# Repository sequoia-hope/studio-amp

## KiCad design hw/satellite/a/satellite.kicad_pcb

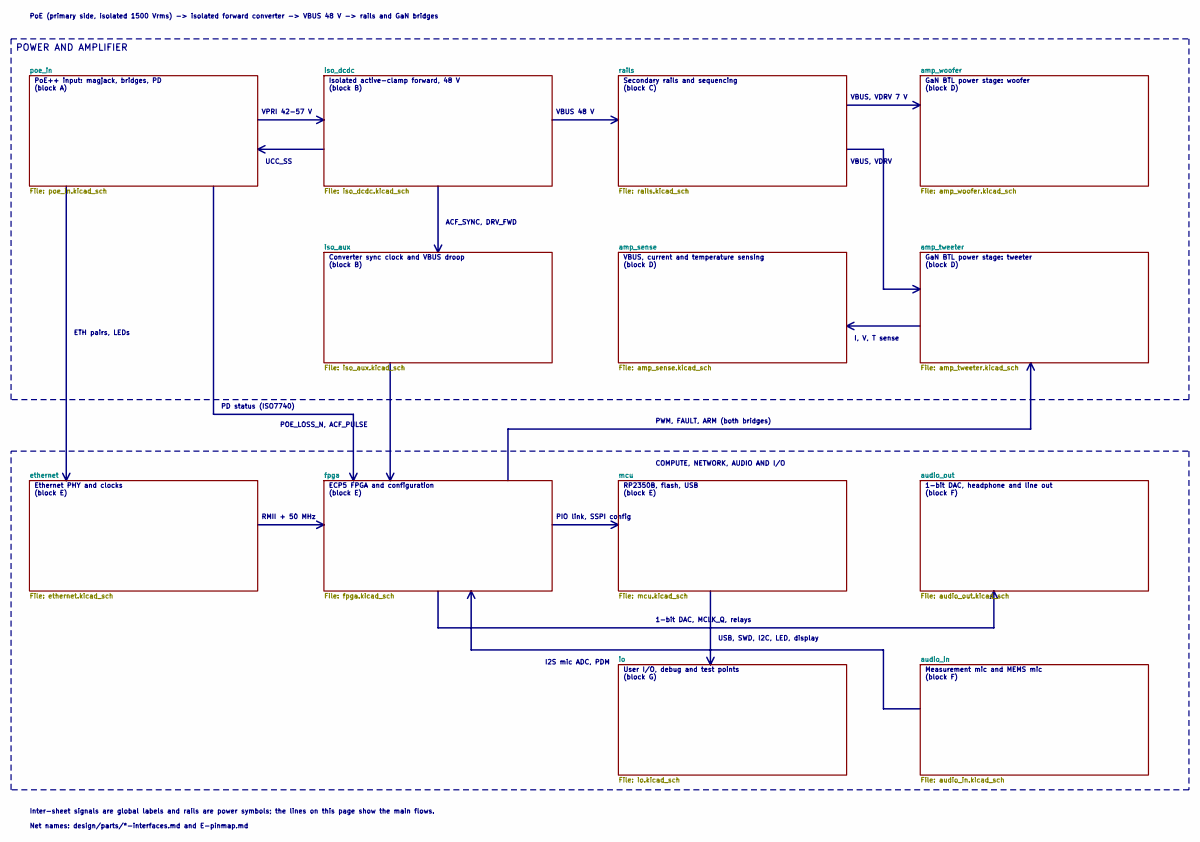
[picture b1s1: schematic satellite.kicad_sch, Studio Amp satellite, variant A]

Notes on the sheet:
PoE++ input: magjack, bridges, PD (block A)
Isolated active-clamp forward, 48 V (block B)
Converter sync clock and VBUS droop (block B)
Secondary rails and sequencing (block C)
GaN BTL power stage: woofer (block D)
GaN BTL power stage: tweeter (block D)
VBUS, current and temperature sensing (block D)
RP2350B, flash, USB (block E)
ECP5 FPGA and configuration (block E)
Ethernet PHY and clocks (block E)
1-bit DAC, headphone and line out (block F)
Measurement mic and MEMS mic (block F)
User I/O, debug and test points (block G)
VPRI 42-57 V
UCC_SS
VBUS 48 V
VBUS, VDRV 7 V
VBUS, VDRV
ACF_SYNC, DRV_FWD
I, V, T sense
ETH pairs, LEDs
RMII + 50 MHz
PIO link, SSPI config
PWM, FAULT, ARM (both bridges)
POE_LOSS_N, ACF_PULSE
1-bit DAC, MCLK_Q, relays
I2S mic ADC, PDM
USB, SWD, I2C, LED, display
PD status (ISO7740)
POWER AND AMPLIFIER
PoE (primary side, isolated 1500 Vrms) -> isolated forward converter -> VBUS 48 V -> rails and GaN bridges
Inter-sheet signals are global labels and rails are power symbols; the lines on this page show the main flows.
Net names: design/parts/*-interfaces.md and E-pinmap.md
COMPUTE, NETWORK, AUDIO AND I/O

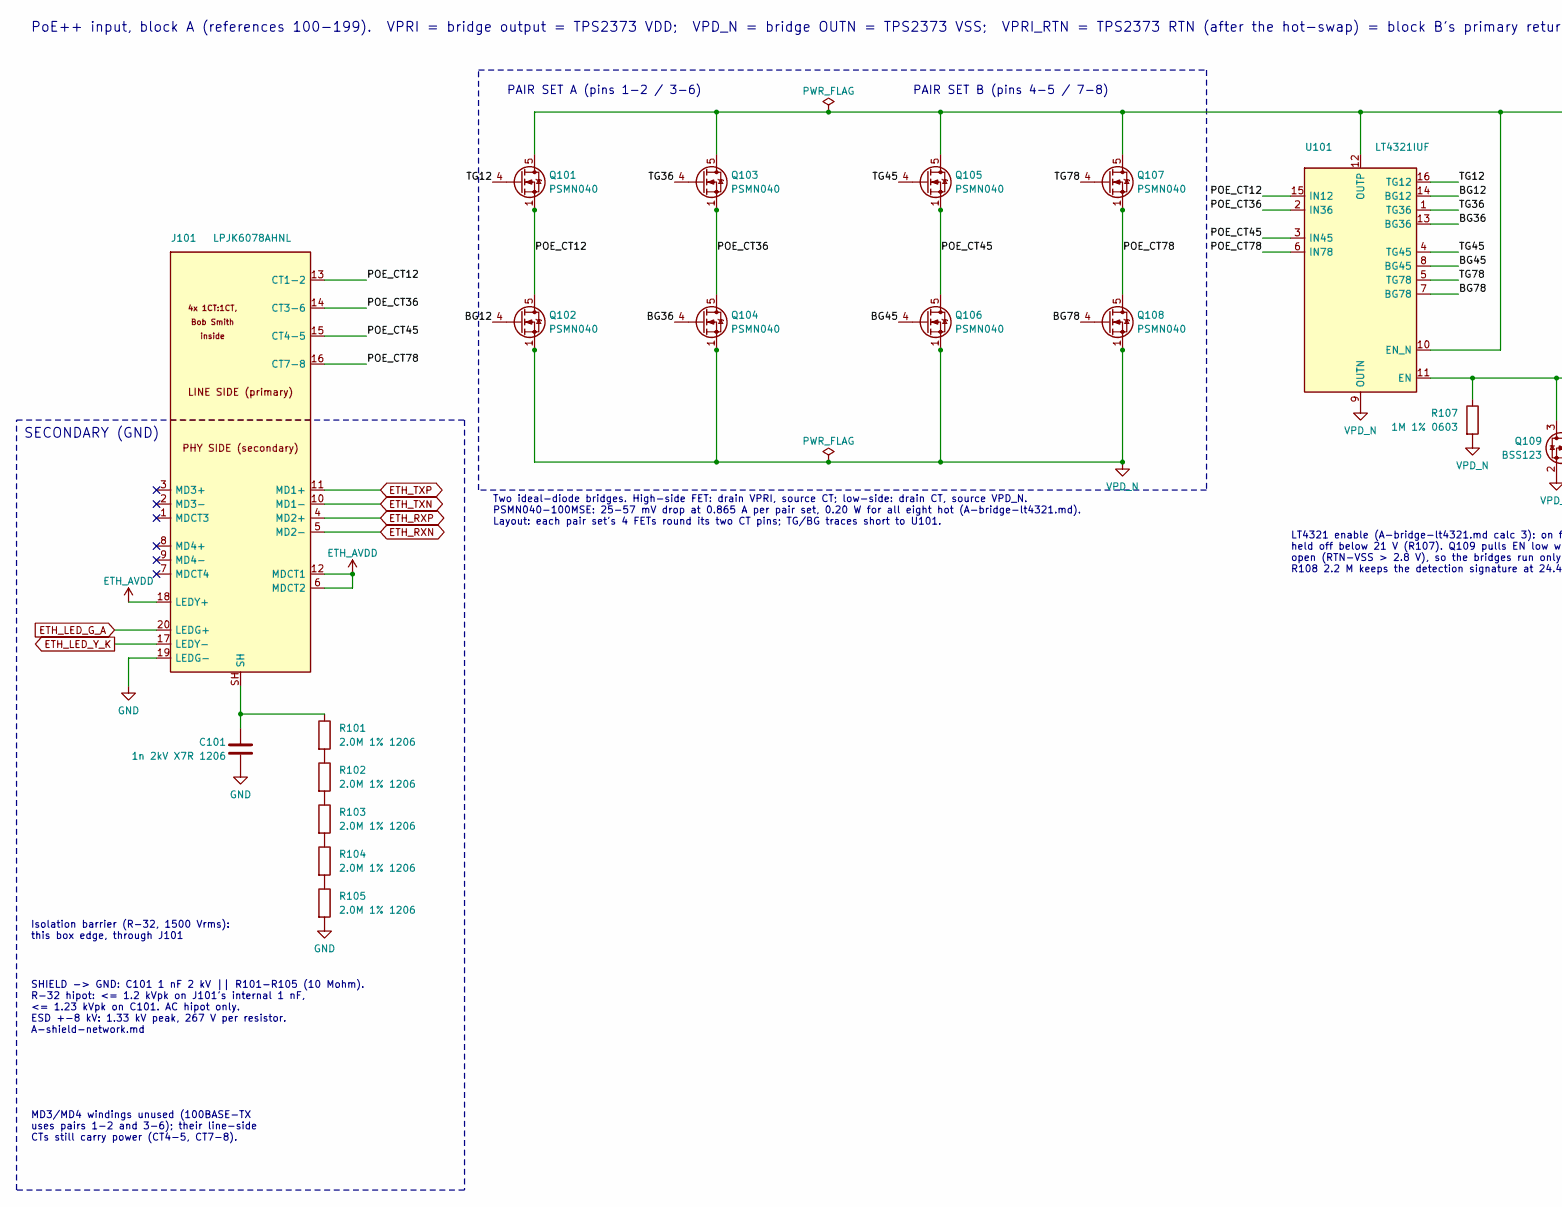
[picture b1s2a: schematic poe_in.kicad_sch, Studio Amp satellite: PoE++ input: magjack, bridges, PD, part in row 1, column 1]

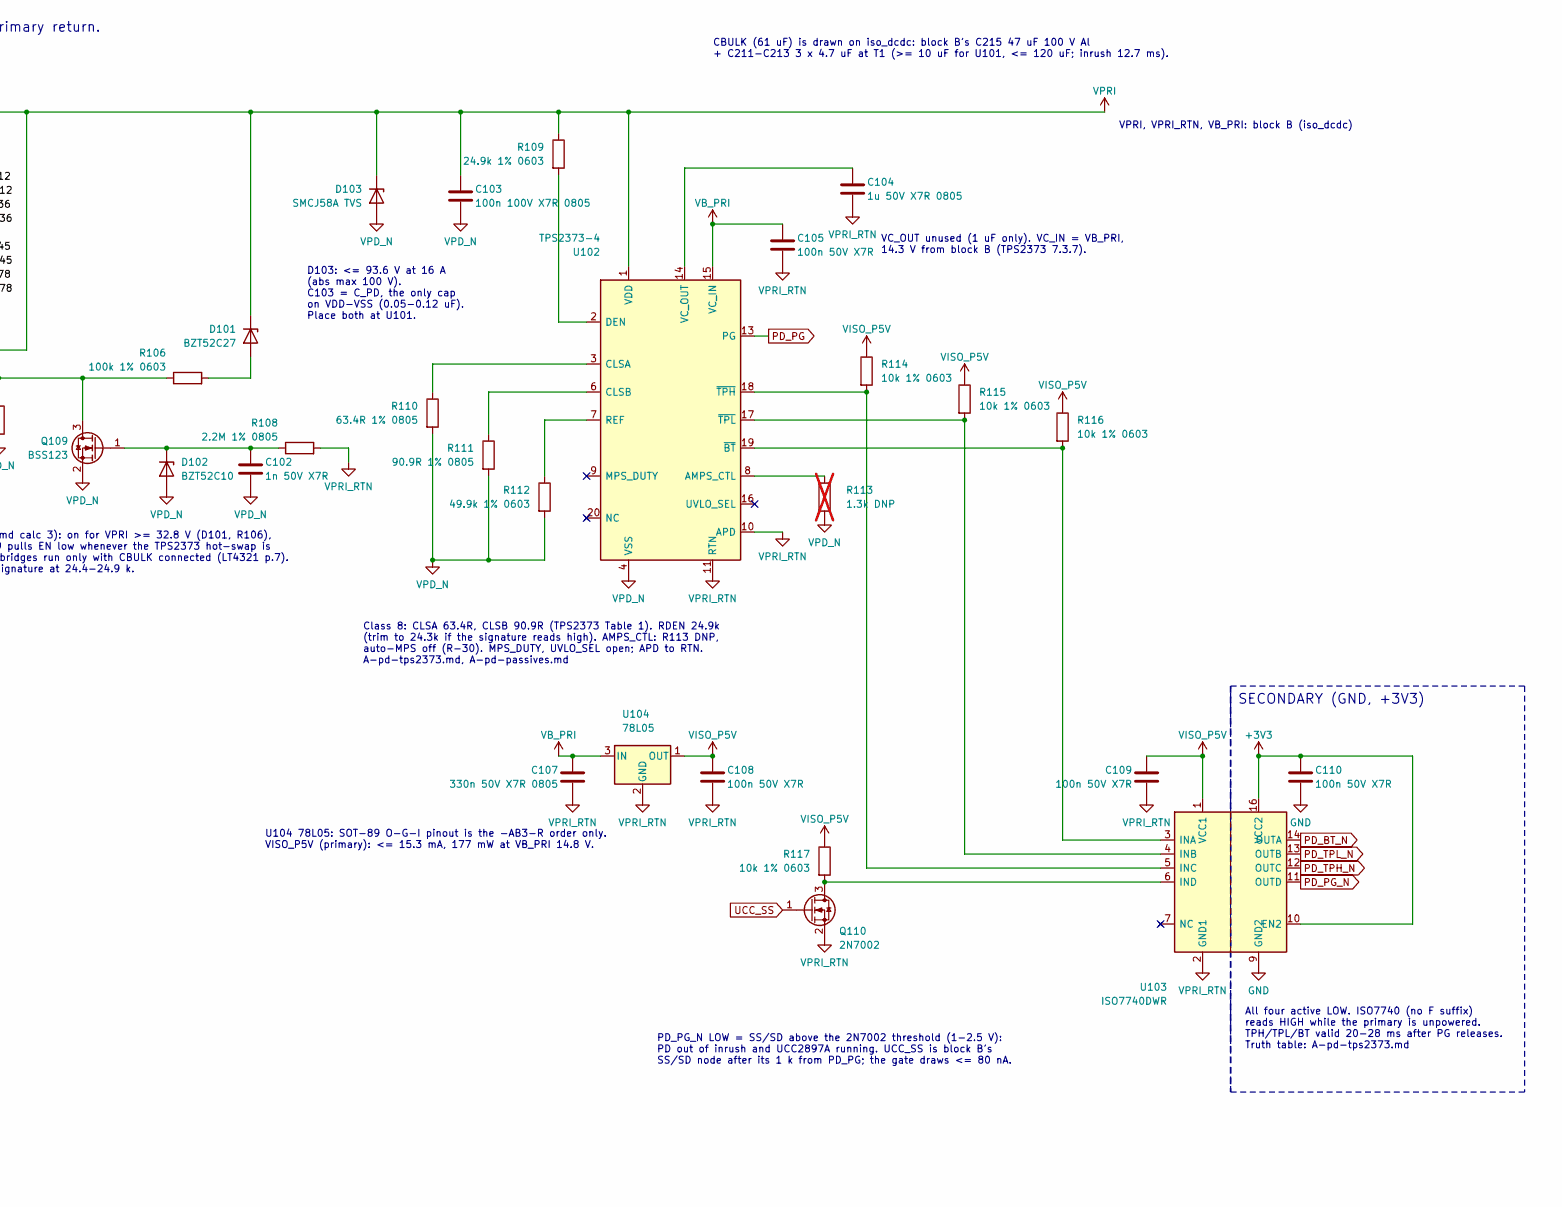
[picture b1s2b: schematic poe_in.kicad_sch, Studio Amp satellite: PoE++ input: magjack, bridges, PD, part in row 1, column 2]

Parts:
C101: 1n 2kV X7R 1206; C_1206_3216Metric; MPN 1206B102K202NT; LCSC C9196
C102: 1n 50V X7R; C_0603_1608Metric; MPN CL10B102KB8NNNC; LCSC C1588
C103: 100n 100V X7R 0805; C_0805_2012Metric; MPN CL21B104KCFNNNE; LCSC C28233
C104: 1u 50V X7R 0805; C_0805_2012Metric; MPN CL21B105KBFNNNE; LCSC C28323
C105, C108, C109, C110: 100n 50V X7R; C_0603_1608Metric; MPN CC0603KRX7R9BB104; LCSC C14663
C107: 330n 50V X7R 0805; C_0805_2012Metric; MPN 0805B334K500NT; LCSC C1740
D101: BZT52C27; D_SOD-123; MPN BZT52C27; LCSC C173421
D102: BZT52C10; D_SOD-123; MPN BZT52C10; LCSC C173431
D103: SMCJ58A TVS; D_SMC; MPN SMCJ58A-13-F; LCSC C135180
J101: LPJK6078AHNL; LINKPP_LPJK6078AHNL_RJ45_PoE; MPN LPJK6078AHNL; LCSC C49274795
Q101, Q102, Q103, Q104, Q105, Q106, Q107, Q108: PSMN040; LFPAK33; MPN PSMN040-100MSEX; LCSC C458214
Q109: BSS123; SOT-23; MPN BSS123,215; LCSC C78962
Q110: 2N7002; SOT-23; MPN 2N7002; LCSC C8545
R101, R102, R103, R104, R105: 2.0M 1% 1206; R_1206_3216Metric; MPN FRC1206F2004TS; LCSC C2907380
R106: 100k 1% 0603; R_0603_1608Metric; MPN 0603WAF1003T5E; LCSC C25803
R107: 1M 1% 0603; R_0603_1608Metric; MPN 0603WAF1004T5E; LCSC C22935
R108: 2.2M 1% 0805; R_0805_2012Metric; MPN 0805W8F2204T5E; LCSC C26113
R109: 24.9k 1% 0603; R_0603_1608Metric; MPN 0603WAF2492T5E; LCSC C25962
R110: 63.4R 1% 0805; R_0805_2012Metric; MPN FRC0805F63R4TS; LCSC C5159721
R111: 90.9R 1% 0805; R_0805_2012Metric; MPN FRC0805F90R9TS; LCSC C3000584
R112: 49.9k 1% 0603; R_0603_1608Metric; MPN 0603WAF4992T5E; LCSC C23184
R113: 1.3k DNP; R_1206_3216Metric; MPN FRC1206F1301TS; LCSC C2933592; not fitted
R114, R115, R116, R117: 10k 1% 0603; R_0603_1608Metric; MPN 0603WAF1002T5E; LCSC C25804
U101: LT4321IUF; QFN-16-1EP_4x4mm_P0.65mm_EP2.15x2.15mm; MPN LT4321IUF#TRPBF; LCSC C580183
U102: TPS2373-4; TI_RGW0020B_VQFN-20-1EP_5x5mm_P0.65mm_EP2.2x2.2mm; MPN TPS2373-4RGWR; LCSC C470963
U103: ISO7740DWR; SOIC-16W_7.5x10.3mm_P1.27mm; MPN ISO7740DWR; LCSC C529547
U104: 78L05; SOT-89-3; MPN 78L05G-AB3-R; LCSC C71136

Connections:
/poe_in/BG12: Q102.4 (G), U101.14 (BG12)
/poe_in/BG36: Q104.4 (G), U101.13 (BG36)
/poe_in/BG45: Q106.4 (G), U101.8 (BG45)
/poe_in/BG78: Q108.4 (G), U101.7 (BG78)
/poe_in/POE_CT12: J101.13 (CT1-2), Q101.1 (S), Q101.2 (S), Q101.3 (S), Q102.5 (D), U101.15 (IN12)
/poe_in/POE_CT36: J101.14 (CT3-6), Q103.1 (S), Q103.2 (S), Q103.3 (S), Q104.5 (D), U101.2 (IN36)
/poe_in/POE_CT45: J101.15 (CT4-5), Q105.1 (S), Q105.2 (S), Q105.3 (S), Q106.5 (D), U101.3 (IN45)
/poe_in/POE_CT78: J101.16 (CT7-8), Q107.1 (S), Q107.2 (S), Q107.3 (S), Q108.5 (D), U101.6 (IN78)
/poe_in/TG12: Q101.4 (G), U101.16 (TG12)
/poe_in/TG36: Q103.4 (G), U101.1 (TG36)
/poe_in/TG45: Q105.4 (G), U101.4 (TG45)
/poe_in/TG78: Q107.4 (G), U101.5 (TG78)
ETH_LED_G_A: J101.20 (LEDG+); also elsewhere on the board
ETH_LED_Y_K: J101.17 (LEDY-); also elsewhere on the board
ETH_RXN: J101.5 (MD2-); also elsewhere on the board
ETH_RXP: J101.4 (MD2+); also elsewhere on the board
ETH_TXN: J101.10 (MD1-); also elsewhere on the board
ETH_TXP: J101.11 (MD1+); also elsewhere on the board
unnamed: C101.1, J101.SH, R101.1
unnamed: D101.2 (A), R106.2
unnamed: C102.1, D102.1 (K), Q109.1 (G), R108.1
unnamed: Q109.3 (D), R106.1, R107.1, U101.11 (EN)
unnamed: Q110.3 (D), R117.2, U103.6 (IND)
unnamed: R101.2, R102.1
unnamed: R102.2, R103.1
unnamed: R103.2, R104.1
unnamed: R104.2, R105.1
unnamed: R113.1, U102.8 (AMPS_CTL)
unnamed: R110.1, U102.3 (CLSA)
unnamed: R111.1, U102.6 (CLSB)
unnamed: R109.2, U102.2 (DEN)
unnamed: R112.1, U102.7 (REF)
unnamed: C104.1, U102.14 (VC_OUT)
unnamed: R116.2, U102.19 (~BT), U103.3 (INA)
unnamed: R114.2, U102.18 (~TPH), U103.5 (INC)
unnamed: R115.2, U102.17 (~TPL), U103.4 (INB)
PD_BT_N: U103.14 (OUTA); also elsewhere on the board
PD_PG: U102.13 (PG); also elsewhere on the board
PD_PG_N: U103.11 (OUTD); also elsewhere on the board
PD_TPH_N: U103.12 (OUTC); also elsewhere on the board
PD_TPL_N: U103.13 (OUTB); also elsewhere on the board
UCC_SS: Q110.1 (G); also elsewhere on the board
VISO_P5V: C108.1, C109.1, R114.1, R115.1, R116.1, R117.1, U103.1 (VCC1), U104.1 (OUT)
VPD_N: C102.2, C103.2, D102.2 (A), D103.2 (A), Q102.1 (S), Q102.2 (S), Q102.3 (S), Q104.1 (S), Q104.2 (S), Q104.3 (S), Q106.1 (S), Q106.2 (S), Q106.3 (S), Q108.1 (S), Q108.2 (S), Q108.3 (S), Q109.2 (S), R107.2, R110.2, R111.2, R112.2, R113.2, U101.9 (OUTN), U101.17 (OUTN), U102.4 (VSS), U102.5 (VSS), U102.21 (VSS)
VPRI: C103.1, D101.1 (K), D103.1 (K), Q101.5 (D), Q103.5 (D), Q105.5 (D), Q107.5 (D), R109.1, U101.10 (EN_N), U101.12 (OUTP), U102.1 (VDD); also elsewhere on the board
VPRI_RTN: C104.2, C105.2, C107.2, C108.2, C109.2, Q110.2 (S), R108.2, U102.10 (APD), U102.11 (RTN), U102.12 (RTN), U103.2 (GND1), U103.8 (GND1), U104.2 (GND); also elsewhere on the board

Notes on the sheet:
PoE++ input, block A (references 100-199). VPRI = bridge output = TPS2373 VDD; VPD_N = bridge OUTN = TPS2373 VSS; VPRI_RTN = TPS2373 RTN (after the hot-swap) = block B's primary return.
SHIELD -> GND: C101 1 nF 2 kV || R101-R105 (10 Mohm). R-32 hipot: <= 1.2 kVpk on J101's internal 1 nF, <= 1.23 kVpk on C101. AC hipot only. ESD +-8 kV: 1.33 kV peak, 267 V per resistor. A-shield-network.md
MD3/MD4 windings unused (100BASE-TX uses pairs 1-2 and 3-6); their line-side CTs still carry power (CT4-5, CT7-8).
SECONDARY (GND)
Isolation barrier (R-32, 1500 Vrms): this box edge, through J101
PAIR SET A (pins 1-2 / 3-6)
PAIR SET B (pins 4-5 / 7-8)
Two ideal-diode bridges. High-side FET: drain VPRI, source CT; low-side: drain CT, source VPD_N. PSMN040-100MSE: 25-57 mV drop at 0.865 A per pair set, 0.20 W for all eight hot (A-bridge-lt4321.md). Layout: each pair set's 4 FETs round its two CT pins; TG/BG traces short to U101.
LT4321 enable (A-bridge-lt4321.md calc 3): on for VPRI >= 32.8 V (D101, R106), held off below 21 V (R107). Q109 pulls EN low whenever the TPS2373 hot-swap is open (RTN-VSS > 2.8 V), so the bridges run only with CBULK connected (LT4321 p.7). R108 2.2 M keeps the detection signature at 24.4-24.9 k.
D103: <= 93.6 V at 16 A (abs max 100 V). C103 = C_PD, the only cap on VDD-VSS (0.05-0.12 uF). Place both at U101.
Class 8: CLSA 63.4R, CLSB 90.9R (TPS2373 Table 1). RDEN 24.9k (trim to 24.3k if the signature reads high). AMPS_CTL: R113 DNP, auto-MPS off (R-30). MPS_DUTY, UVLO_SEL open; APD to RTN. A-pd-tps2373.md, A-pd-passives.md
VC_OUT unused (1 uF only). VC_IN = VB_PRI, 14.3 V from block B (TPS2373 7.3.7).
CBULK (61 uF) is drawn on iso_dcdc: block B's C215 47 uF 100 V Al + C211-C213 3 x 4.7 uF at T1 (>= 10 uF for U101, <= 120 uF; inrush 12.7 ms).
VPRI, VPRI_RTN, VB_PRI: block B (iso_dcdc)
PD_PG_N LOW = SS/SD above the 2N7002 threshold (1-2.5 V): PD out of inrush and UCC2897A running. UCC_SS is block B's SS/SD node after its 1 k from PD_PG; the gate draws <= 80 nA.
U104 78L05: SOT-89 O-G-I pinout is the -AB3-R order only. VISO_P5V (primary): <= 15.3 mA, 177 mW at VB_PRI 14.8 V.
SECONDARY (GND, +3V3)
All four active LOW. ISO7740 (no F suffix) reads HIGH while the primary is unpowered. TPH/TPL/BT valid 20-28 ms after PG releases. Truth table: A-pd-tps2373.md

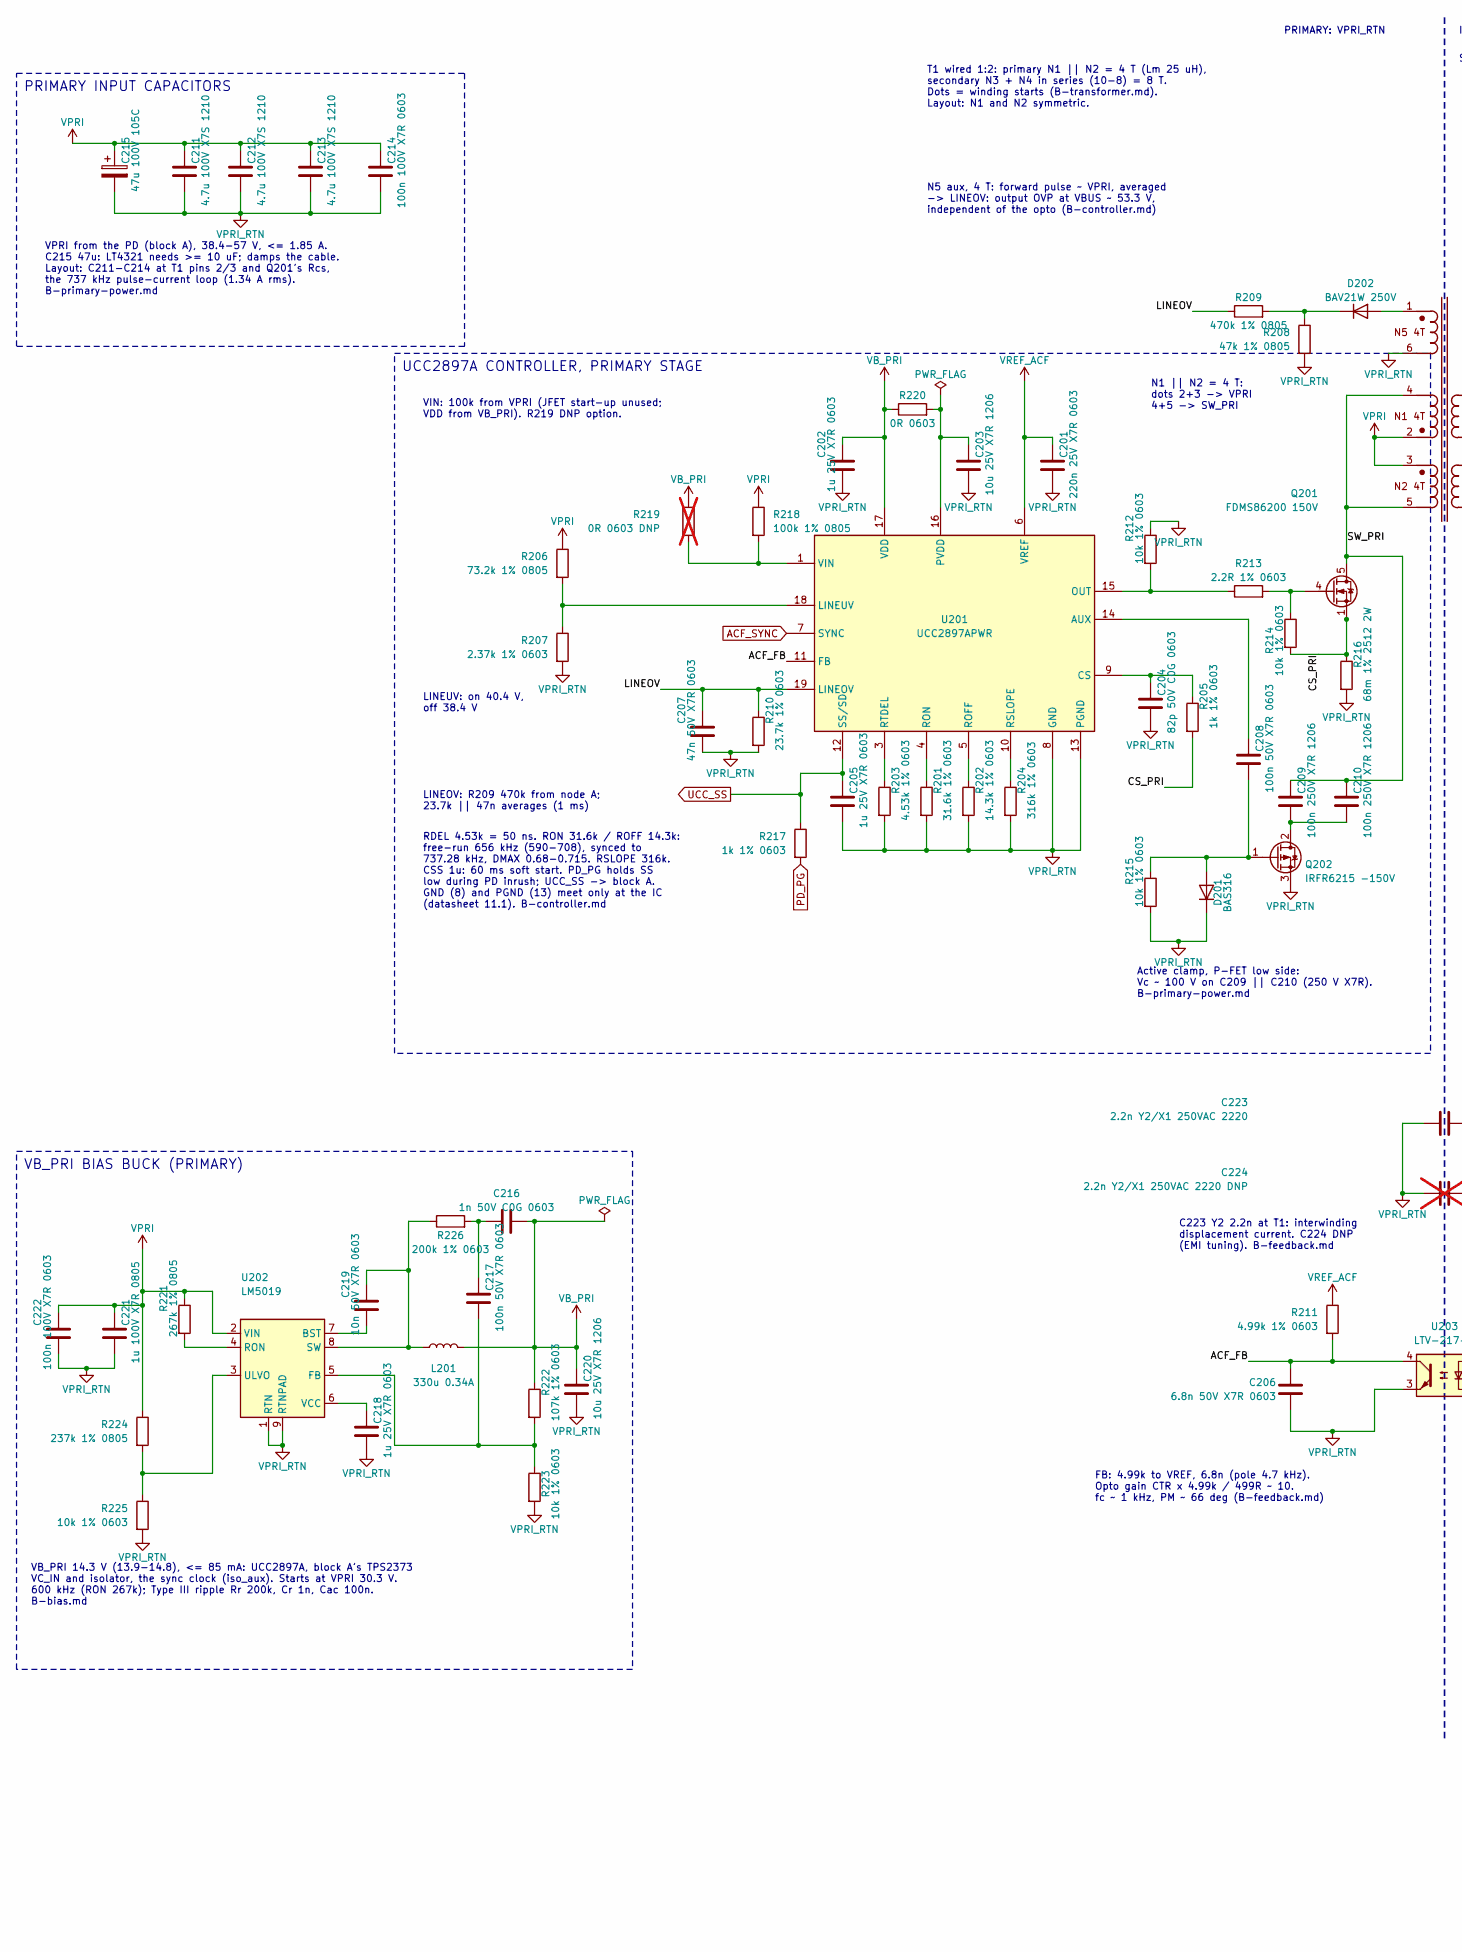
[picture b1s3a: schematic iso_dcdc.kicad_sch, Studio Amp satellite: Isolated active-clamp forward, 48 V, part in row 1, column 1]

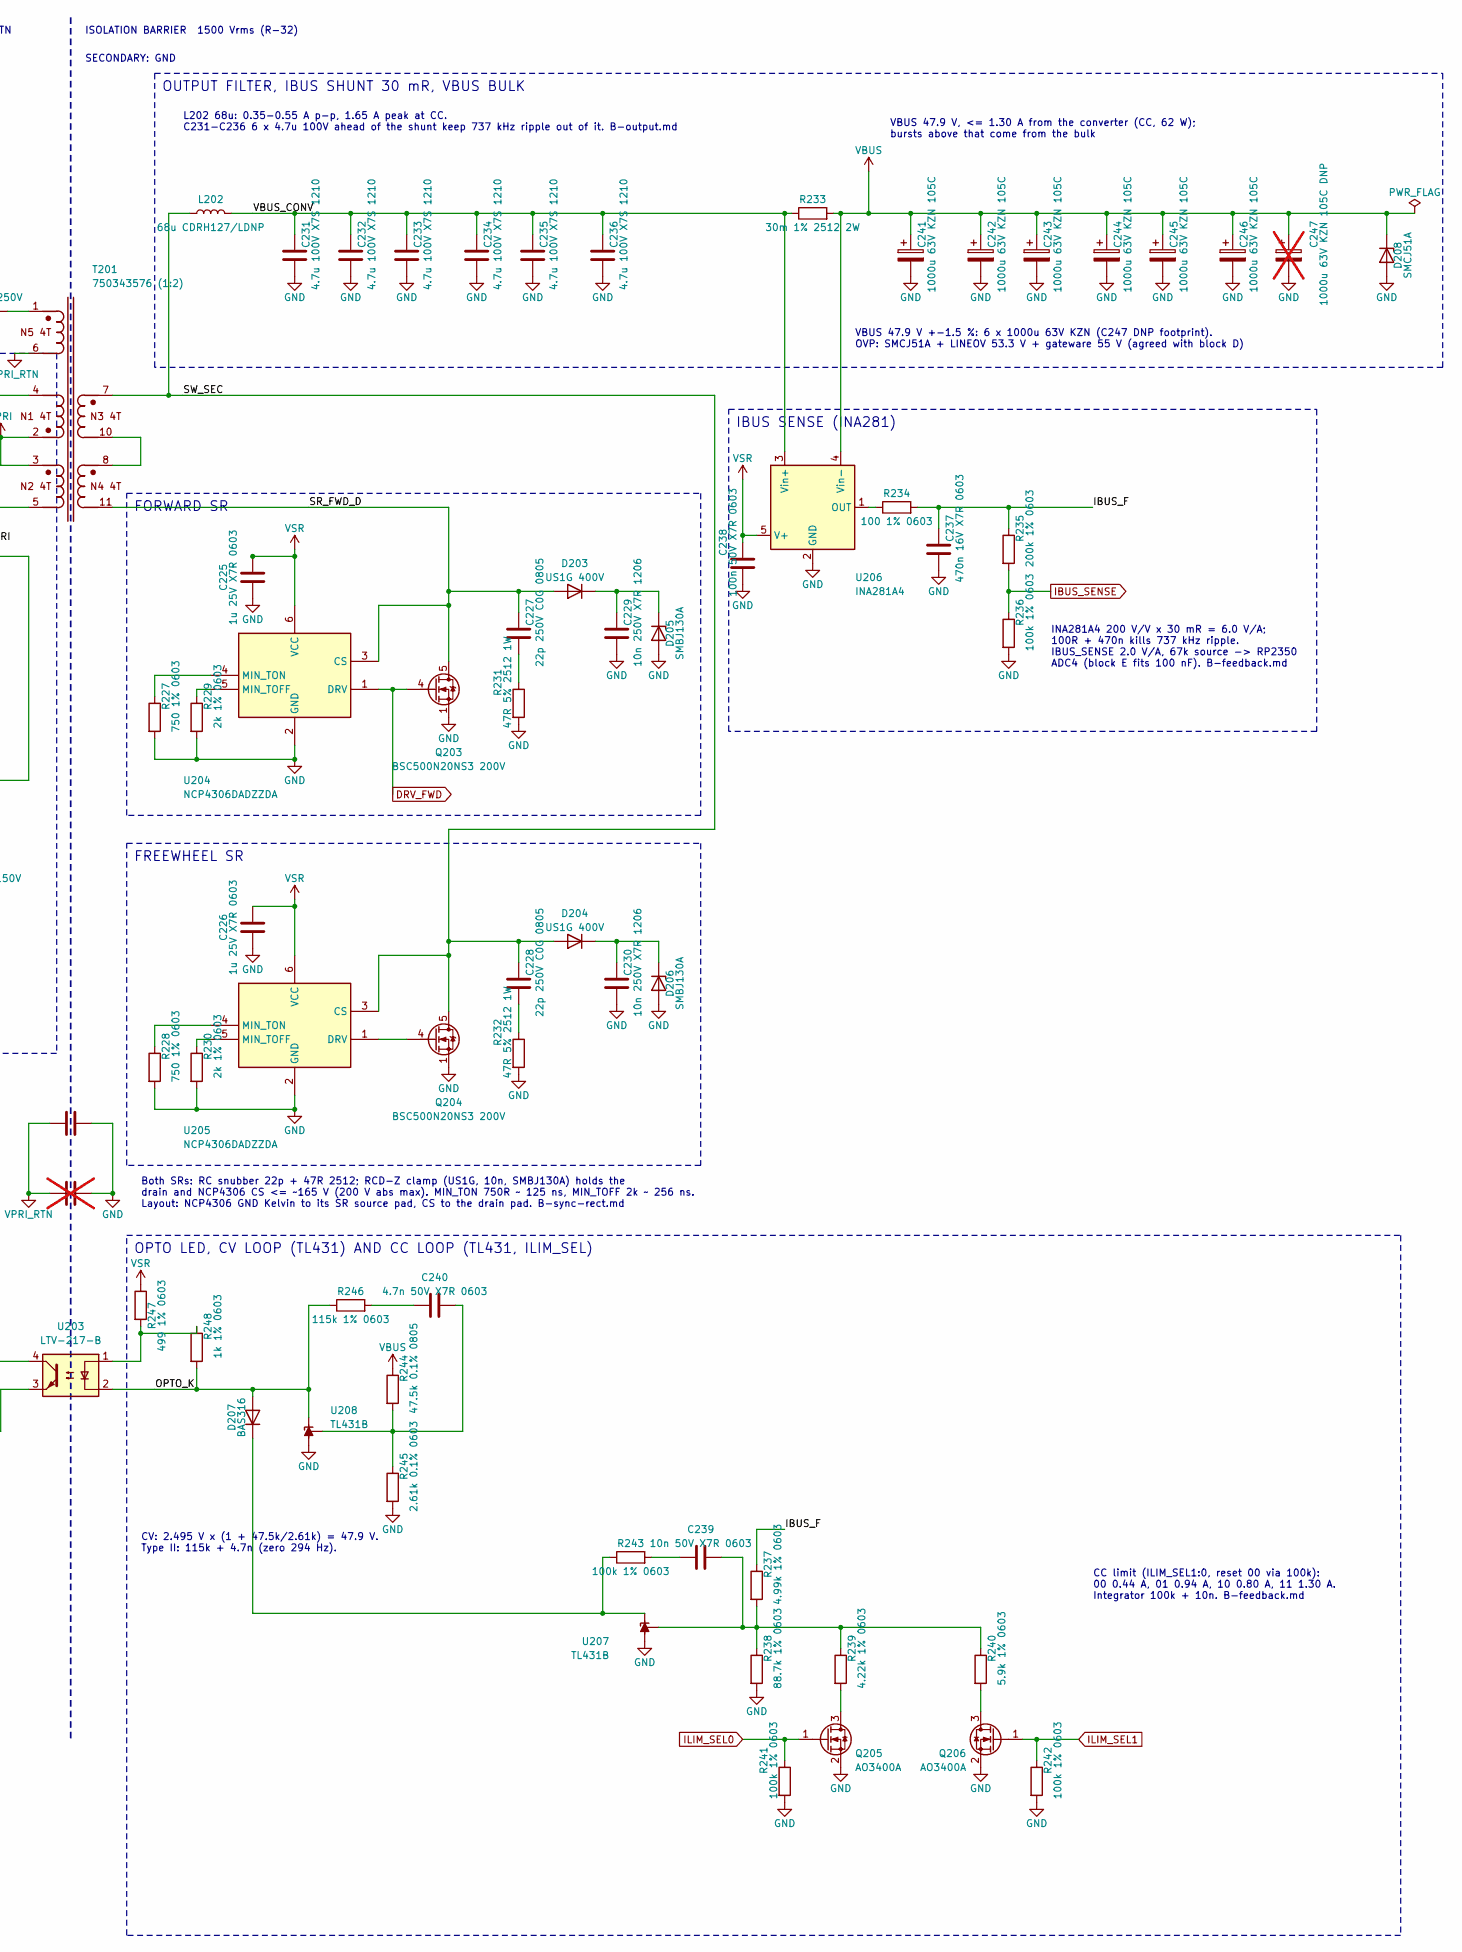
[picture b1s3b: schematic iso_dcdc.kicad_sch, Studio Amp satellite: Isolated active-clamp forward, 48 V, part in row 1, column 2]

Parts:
C201: 220n 25V X7R 0603; C_0603_1608Metric; MPN CL10B224KA8NNNC; LCSC C21120
C202, C205, C218, C225, C226: 1u 25V X7R 0603; C_0603_1608Metric; MPN CL10B105KA8NNNC; LCSC C29936
C203, C220: 10u 25V X7R 1206; C_1206_3216Metric; MPN CL31B106KAHNNNE; LCSC C14860
C204: 82p 50V C0G 0603; C_0603_1608Metric; MPN 0603CG820J500NT; LCSC C1683
C206: 6.8n 50V X7R 0603; C_0603_1608Metric; MPN 0603B682K500NT; LCSC C1631
C207: 47n 50V X7R 0603; C_0603_1608Metric; MPN CL10B473KB8NNNC; LCSC C1622
C208, C217, C238: 100n 50V X7R 0603; C_0603_1608Metric; MPN CL10B104KB8NNNC; LCSC C1591
C209, C210: 100n 250V X7R 1206; C_1206_3216Metric; MPN GRM31CR72E104KW03L; LCSC C97956
C211, C212, C213, C231, C232, C233, C234, C235, C236: 4.7u 100V X7S 1210; C_1210_3225Metric; MPN GCM32DC72A475KE02L; LCSC C913445
C214, C222: 100n 100V X7R 0603; C_0603_1608Metric; MPN CL10B104KC8NNNC; LCSC C15725
C215: 47u 100V 105C; CP_Elec_10x10.5; MPN RVT2A470M1010; LCSC C87862
C216: 1n 50V C0G 0603; C_0603_1608Metric; MPN CL10C102JB8NNNC; LCSC C163508
C219, C239: 10n 50V X7R 0603; C_0603_1608Metric; MPN CL10B103KB8NNNC; LCSC C1589
C221: 1u 100V X7R 0805; C_0805_2012Metric; MPN HMK212BC7105KGHTE; LCSC C385977
C223: 2.2n Y2/X1 250VAC 2220; C_2220_5750Metric; MPN GA355QR7GF222KW01L; LCSC C91600
C224: 2.2n Y2/X1 250VAC 2220 DNP; C_2220_5750Metric; MPN GA355QR7GF222KW01L; LCSC C91600; not fitted
C227, C228: 22p 250V C0G 0805; C_0805_2012Metric; MPN CC0805JRNPOYBN220; LCSC C90626
C229, C230: 10n 250V X7R 1206; C_1206_3216Metric; MPN 1206B103K251NT; LCSC C913956
C237: 470n 16V X7R 0603; C_0603_1608Metric; MPN CL10B474KO8NNNC; LCSC C105526
C240: 4.7n 50V X7R 0603; C_0603_1608Metric; MPN CL10B472KB8NNNC; LCSC C1621
C241, C242, C243, C244, C245, C246: 1000u 63V KZN 105C; CP_Radial_D16.0mm_P7.50mm; MPN EKZN630ELL102ML25S; LCSC C337254
C247: 1000u 63V KZN 105C DNP; CP_Radial_D16.0mm_P7.50mm; MPN EKZN630ELL102ML25S; LCSC C337254; not fitted
D201, D207: BAS316; D_SOD-323; MPN BAS316,115; LCSC C109218
D202: BAV21W 250V; D_SOD-123; MPN BAV21W; LCSC C113947
D203, D204: US1G 400V; D_SMA; MPN US1G; LCSC C383015
D205, D206: SMBJ130A; D_SMB; MPN SMBJ130A-E3/52; LCSC C553984
D208: SMCJ51A; D_SMC; MPN SMCJ51A; LCSC C408371
L201: 330u 0.34A; L_SXN_SM5845; MPN SM5845-331MT; LCSC C10124
L202: 68u CDRH127/LDNP; L_Sumida_CDRH127; MPN CDRH127/LDNP-680MC; LCSC C2452974
Q201: FDMS86200 150V; Infineon_PG-TDSON-8_6.15x5.15mm; MPN FDMS86200; LCSC C128799
Q202: IRFR6215 -150V; TO-252-2; MPN IRFR6215TRLPBF; LCSC C537989
Q203, Q204: BSC500N20NS3 200V; Infineon_PG-TDSON-8_6.15x5.15mm; MPN BSC500N20NS3GATMA1; LCSC C5381902
Q205, Q206: AO3400A; SOT-23; MPN AO3400A; LCSC C20917
R201: 31.6k 1% 0603; R_0603_1608Metric; MPN 0603WAF3162T5E; LCSC C25967
R202: 14.3k 1% 0603; R_0603_1608Metric; MPN 0603WAF1432T5E; LCSC C22799
R203: 4.53k 1% 0603; R_0603_1608Metric; MPN 0603WAF4531T5E; LCSC C25971
R204: 316k 1% 0603; R_0603_1608Metric; MPN 0603WAF3163T5E; LCSC C25814
R205, R217, R248: 1k 1% 0603; R_0603_1608Metric; MPN 0603WAF1001T5E; LCSC C21190
R206: 73.2k 1% 0805; R_0805_2012Metric; MPN 0805W8F7322T5E; LCSC C17814
R207: 2.37k 1% 0603; R_0603_1608Metric; MPN 0603WAF2371T5E; LCSC C25964
R208: 47k 1% 0805; R_0805_2012Metric; MPN 0805W8F4702T5E; LCSC C17713
R209: 470k 1% 0805; R_0805_2012Metric; MPN 0805W8F4703T5E; LCSC C17709
R210: 23.7k 1% 0603; R_0603_1608Metric; MPN 0603WAF2372T5E; LCSC C22912
R211, R237: 4.99k 1% 0603; R_0603_1608Metric; MPN 0603WAF4991T5E; LCSC C23046
R212, R214, R215, R223, R225: 10k 1% 0603; R_0603_1608Metric; MPN 0603WAF1002T5E; LCSC C25804
R213: 2.2R 1% 0603; R_0603_1608Metric; MPN RC0603FR-072R2L; LCSC C112307
R216: 68m 1% 2512 2W; R_2512_6332Metric; MPN RLP25FEER068; LCSC C2683389
R218: 100k 1% 0805; R_0805_2012Metric; MPN 0805W8F1003T5E; LCSC C149504
R219: 0R 0603 DNP; R_0603_1608Metric; MPN 0603WAF0000T5E; LCSC C21189; not fitted
R220: 0R 0603; R_0603_1608Metric; MPN 0603WAF0000T5E; LCSC C21189
R221: 267k 1% 0805; R_0805_2012Metric; MPN 0805W8F2673T5E; LCSC C17585
R222: 107k 1% 0603; R_0603_1608Metric; MPN 0603WAF1073T5E; LCSC C14889
R224: 237k 1% 0805; R_0805_2012Metric; MPN 0805W8F2373T5E; LCSC C17568
R226, R235: 200k 1% 0603; R_0603_1608Metric; MPN 0603WAF2003T5E; LCSC C25811
R227, R228: 750 1% 0603; R_0603_1608Metric; MPN 0603WAF7500T5E; LCSC C23241
R229, R230: 2k 1% 0603; R_0603_1608Metric; MPN 0603WAF2001T5E; LCSC C22975
R231, R232: 47R 5% 2512 1W; R_2512_6332Metric; MPN 25121WJ0470T4E; LCSC C15261
R233: 30m 1% 2512 2W; R_2512_6332Metric; MPN LR122WF300MT4E; LCSC C2941066
R234: 100 1% 0603; R_0603_1608Metric; MPN 0603WAF1000T5E; LCSC C22775
R236, R241, R242, R243: 100k 1% 0603; R_0603_1608Metric; MPN 0603WAF1003T5E; LCSC C25803
R238: 88.7k 1% 0603; R_0603_1608Metric; MPN 0603WAF8872T5E; LCSC C23258
R239: 4.22k 1% 0603; R_0603_1608Metric; MPN 0603WAF4221T5E; LCSC C23042
R240: 5.9k 1% 0603; R_0603_1608Metric; MPN 0603WAF5901T5E; LCSC C23071
R244: 47.5k 0.1% 0805; R_0805_2012Metric; MPN RT0805BRD0747K5L; LCSC C865514
R245: 2.61k 0.1% 0603; R_0603_1608Metric; MPN RT0603BRD072K61L; LCSC C861301
R246: 115k 1% 0603; R_0603_1608Metric; MPN 0603WAF1153T5E; LCSC C22783
R247: 499 1% 0603; R_0603_1608Metric; MPN 0603WAF4990T5E; LCSC C23065
T201: 750343576 (1:2); Wurth_750343576_ER19; MPN 750343576; LCSC HAND
U201: UCC2897APWR; TSSOP-20_4.4x6.5mm_P0.65mm; MPN UCC2897APWR; LCSC C54444
U202: LM5019; SOIC-8-1EP_3.9x4.9mm_P1.27mm_EP2.95x4.9mm_Mask2.71x3.4mm; MPN LM5019MRX/NOPB; LCSC C471034
U203: LTV-217-B; SOP-4_4.4x2.6mm_P1.27mm; MPN LTV-217-B-G; LCSC C115450
U204, U205: NCP4306DADZZDA; SOT-23-6; MPN NCP4306DADZZDASNT1G; LCSC C504885
U206: INA281A4; SOT-23-5; MPN INA281A4IDBVR; LCSC C2864421
U207, U208: TL431B; SOT-23; MPN TL431BIDBZR; LCSC C41283

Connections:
/iso_dcdc/ACF_FB: C206.1, R211.2, U201.11 (FB), U203.4
/iso_dcdc/CS_PRI: Q201.1 (S), Q201.2 (S), Q201.3 (S), R205.2, R214.2, R216.1
/iso_dcdc/IBUS_F: C237.1, R234.2, R235.1, R237.1
/iso_dcdc/LINEOV: C207.1, R209.1, R210.1, U201.19 (LINEOV)
/iso_dcdc/OPTO_K: D207.2 (A), R246.1, R248.2, U203.2, U208.1 (K)
/iso_dcdc/SR_FWD_D: C227.1, D203.2 (A), Q203.5 (D), T201.11 (N4_F), U204.3 (CS)
/iso_dcdc/SW_PRI: C209.1, C210.1, Q201.5 (D), T201.4 (N1_F), T201.5 (N2_F)
/iso_dcdc/SW_SEC: C228.1, D204.2 (A), L202.1, Q204.5 (D), T201.7 (N3_S), U205.3 (CS)
/iso_dcdc/VBUS_CONV: C231.1, C232.1, C233.1, C234.1, C235.1, C236.1, L202.2, R233.1, U206.3 (Vin+)
ACF_SYNC: U201.7 (SYNC); also elsewhere on the board
DRV_FWD: Q203.4 (G), U204.1 (DRV); also elsewhere on the board
IBUS_SENSE: R235.2, R236.1; also elsewhere on the board
ILIM_SEL0: Q205.1 (G), R241.1; also elsewhere on the board
ILIM_SEL1: Q206.1 (G), R242.1; also elsewhere on the board
unnamed: C216.1, C217.1, R226.2
unnamed: C227.2, R231.1
unnamed: C228.2, R232.1
unnamed: C239.1, R243.2
unnamed: C240.1, R246.2
unnamed: C208.2, D201.2 (A), Q202.1 (G), R215.1
unnamed: D202.2 (A), T201.1 (N5_S)
unnamed: D202.1 (K), R208.1, R209.2
unnamed: C229.1, D203.1 (K), D205.1 (K)
unnamed: C230.1, D204.1 (K), D206.1 (K)
unnamed: D207.1 (K), R243.1, U207.1 (K)
unnamed: Q201.4 (G), R213.2, R214.1
unnamed: C209.2, C210.2, Q202.2 (D)
unnamed: Q204.4 (G), U205.1 (DRV)
unnamed: Q205.3 (D), R239.2
unnamed: Q206.3 (D), R240.2
unnamed: R247.2, R248.1, U203.1
unnamed: T201.8 (N4_S), T201.10 (N3_F)
unnamed: C208.1, U201.14 (AUX)
unnamed: C204.1, R205.1, U201.9 (CS)
unnamed: R206.2, R207.1, U201.18 (LINEUV)
unnamed: R212.2, R213.1, U201.15 (OUT)
unnamed: R202.1, U201.5 (ROFF)
unnamed: R201.1, U201.4 (RON)
unnamed: R204.1, U201.10 (RSLOPE)
unnamed: R203.1, U201.3 (RTDEL)
unnamed: R218.2, R219.2, U201.1 (VIN)
unnamed: C219.2, U202.7 (BST)
unnamed: C217.2, R222.2, R223.1, U202.5 (FB)
unnamed: R221.2, U202.4 (RON)
unnamed: C219.1, L201.1, R226.1, U202.8 (SW)
unnamed: R224.2, R225.1, U202.3 (ULVO)
unnamed: C218.1, U202.6 (VCC)
unnamed: R229.1, U204.5 (MIN_TOFF)
unnamed: R227.1, U204.4 (MIN_TON)
unnamed: R230.1, U205.5 (MIN_TOFF)
unnamed: R228.1, U205.4 (MIN_TON)
unnamed: R234.1, U206.1 (OUT)
unnamed: C239.2, R237.2, R238.1, R239.1, R240.1, U207.2 (REF)
unnamed: C240.2, R244.2, R245.1, U208.2 (REF)
PD_PG: R217.2; also elsewhere on the board
UCC_SS: C205.1, R217.1, U201.12 (SS/SD); also elsewhere on the board
VPRI: C211.1, C212.1, C213.1, C214.1, C215.1, C221.1, C222.1, R206.1, R218.1, R221.1, R224.1, T201.2 (N1_S), T201.3 (N2_S), U202.2 (VIN); also elsewhere on the board
VPRI_RTN: C201.2, C202.2, C203.2, C204.2, C205.2, C206.2, C207.2, C211.2, C212.2, C213.2, C214.2, C215.2, C218.2, C220.2, C221.2, C222.2, C223.1, C224.1, D201.1 (K), Q202.3 (S), R201.2, R202.2, R203.2, R204.2, R207.2, R208.2, R210.2, R212.1, R215.2, R216.2, R223.2, R225.2, T201.6 (N5_F), U201.8 (GND), U201.13 (PGND), U202.1 (RTN), U202.9 (RTNPAD), U203.3; also elsewhere on the board
VREF_ACF: C201.1, R211.1, U201.6 (VREF); also elsewhere on the board
VSR: C225.1, C226.1, C238.1, R247.1, U204.6 (VCC), U205.6 (VCC), U206.5 (V+); also elsewhere on the board

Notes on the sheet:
VPRI from the PD (block A), 38.4-57 V, <= 1.85 A. C215 47u: LT4321 needs >= 10 uF; damps the cable. Layout: C211-C214 at T1 pins 2/3 and Q201's Rcs, the 737 kHz pulse-current loop (1.34 A rms). B-primary-power.md
PRIMARY INPUT CAPACITORS
N1 || N2 = 4 T: dots 2+3 -> VPRI 4+5 -> SW_PRI
T1 wired 1:2: primary N1 || N2 = 4 T (Lm 25 uH), secondary N3 + N4 in series (10-8) = 8 T. Dots = winding starts (B-transformer.md). Layout: N1 and N2 symmetric.
N5 aux, 4 T: forward pulse ~ VPRI, averaged -> LINEOV: output OVP at VBUS ~ 53.3 V, independent of the opto (B-controller.md)
Active clamp, P-FET low side: Vc ~ 100 V on C209 || C210 (250 V X7R). B-primary-power.md
VIN: 100k from VPRI (JFET start-up unused; VDD from VB_PRI). R219 DNP option.
LINEUV: on 40.4 V, off 38.4 V
LINEOV: R209 470k from node A; 23.7k || 47n averages (1 ms)
RDEL 4.53k = 50 ns. RON 31.6k / ROFF 14.3k: free-run 656 kHz (590-708), synced to 737.28 kHz, DMAX 0.68-0.715. RSLOPE 316k. CSS 1u: 60 ms soft start. PD_PG holds SS low during PD inrush; UCC_SS -> block A. GND (8) and PGND (13) meet only at the IC (datasheet 11.1). B-controller.md
UCC2897A CONTROLLER, PRIMARY STAGE
VB_PRI 14.3 V (13.9-14.8), <= 85 mA: UCC2897A, block A's TPS2373 VC_IN and isolator, the sync clock (iso_aux). Starts at VPRI 30.3 V. 600 kHz (RON 267k); Type III ripple Rr 200k, Cr 1n, Cac 100n. B-bias.md
VB_PRI BIAS BUCK (PRIMARY)
ISOLATION BARRIER 1500 Vrms (R-32)
PRIMARY: VPRI_RTN
SECONDARY: GND
C223 Y2 2.2n at T1: interwinding displacement current. C224 DNP (EMI tuning). B-feedback.md
FB: 4.99k to VREF, 6.8n (pole 4.7 kHz). Opto gain CTR x 4.99k / 499R ~ 10. fc ~ 1 kHz, PM ~ 66 deg (B-feedback.md)
FORWARD SR
FREEWHEEL SR
Both SRs: RC snubber 22p + 47R 2512; RCD-Z clamp (US1G, 10n, SMBJ130A) holds the drain and NCP4306 CS <= ~165 V (200 V abs max). MIN_TON 750R ~ 125 ns, MIN_TOFF 2k ~ 256 ns. Layout: NCP4306 GND Kelvin to its SR source pad, CS to the drain pad. B-sync-rect.md
VBUS 47.9 V, <= 1.30 A from the converter (CC, 62 W); bursts above that come from the bulk
L202 68u: 0.35-0.55 A p-p, 1.65 A peak at CC. C231-C236 6 x 4.7u 100V ahead of the shunt keep 737 kHz ripple out of it. B-output.md
VBUS 47.9 V +-1.5 %: 6 x 1000u 63V KZN (C247 DNP footprint). OVP: SMCJ51A + LINEOV 53.3 V + gateware 55 V (agreed with block D)
OUTPUT FILTER, IBUS SHUNT 30 mR, VBUS BULK
INA281A4 200 V/V x 30 mR = 6.0 V/A; 100R + 470n kills 737 kHz ripple. IBUS_SENSE 2.0 V/A, 67k source -> RP2350 ADC4 (block E fits 100 nF). B-feedback.md
IBUS SENSE (INA281)
CV: 2.495 V x (1 + 47.5k/2.61k) = 47.9 V. Type II: 115k + 4.7n (zero 294 Hz).
CC limit (ILIM_SEL1:0, reset 00 via 100k): 00 0.44 A, 01 0.94 A, 10 0.80 A, 11 1.30 A. Integrator 100k + 10n. B-feedback.md
OPTO LED, CV LOOP (TL431) AND CC LOOP (TL431, ILIM_SEL)
